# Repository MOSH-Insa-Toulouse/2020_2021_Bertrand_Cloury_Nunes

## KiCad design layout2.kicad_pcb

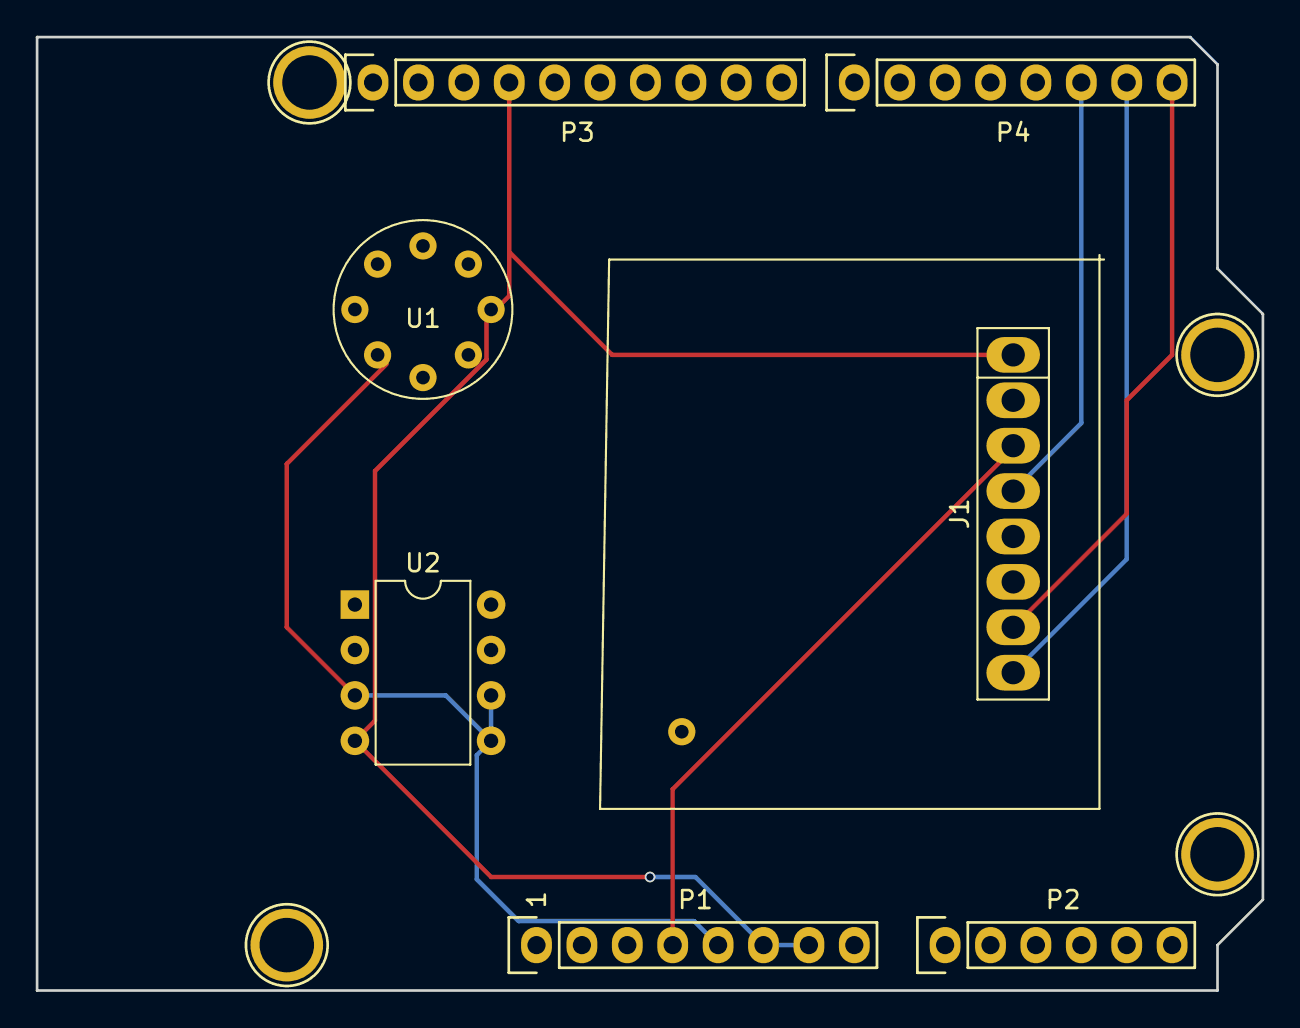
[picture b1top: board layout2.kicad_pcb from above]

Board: 2 copper layers, 68.6 x 53.3 mm, 11 parts (0 on the bottom side), 6 nets.

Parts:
J1: Conn_01x08_Female; RN2483_new
P1: Power; Socket_Strip_Arduino_1x08
P2: Analog; Socket_Strip_Arduino_1x06
P3: Digital; Socket_Strip_Arduino_1x10
P4: Digital; Socket_Strip_Arduino_1x08
P5, P6, P7, P8: CONN_01X01; Arduino_1pin
U1: Capteur_AIME
U2: LTC1100xN8; DIP-8_W7.62mm

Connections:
+3V3: J1.3, P1.4
+5V: P1.5, U1.2, U1.3, U2.3, U2.5, U2.6
/0(Rx): J1.7, P4.8
/1(Tx): J1.8, P4.7
/2: J1.4, P4.6
GND: J1.1, P1.6, P1.7, P3.4, U1.5, U2.4

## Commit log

2020-12-10 modif jg
2021-01-02 Final push
